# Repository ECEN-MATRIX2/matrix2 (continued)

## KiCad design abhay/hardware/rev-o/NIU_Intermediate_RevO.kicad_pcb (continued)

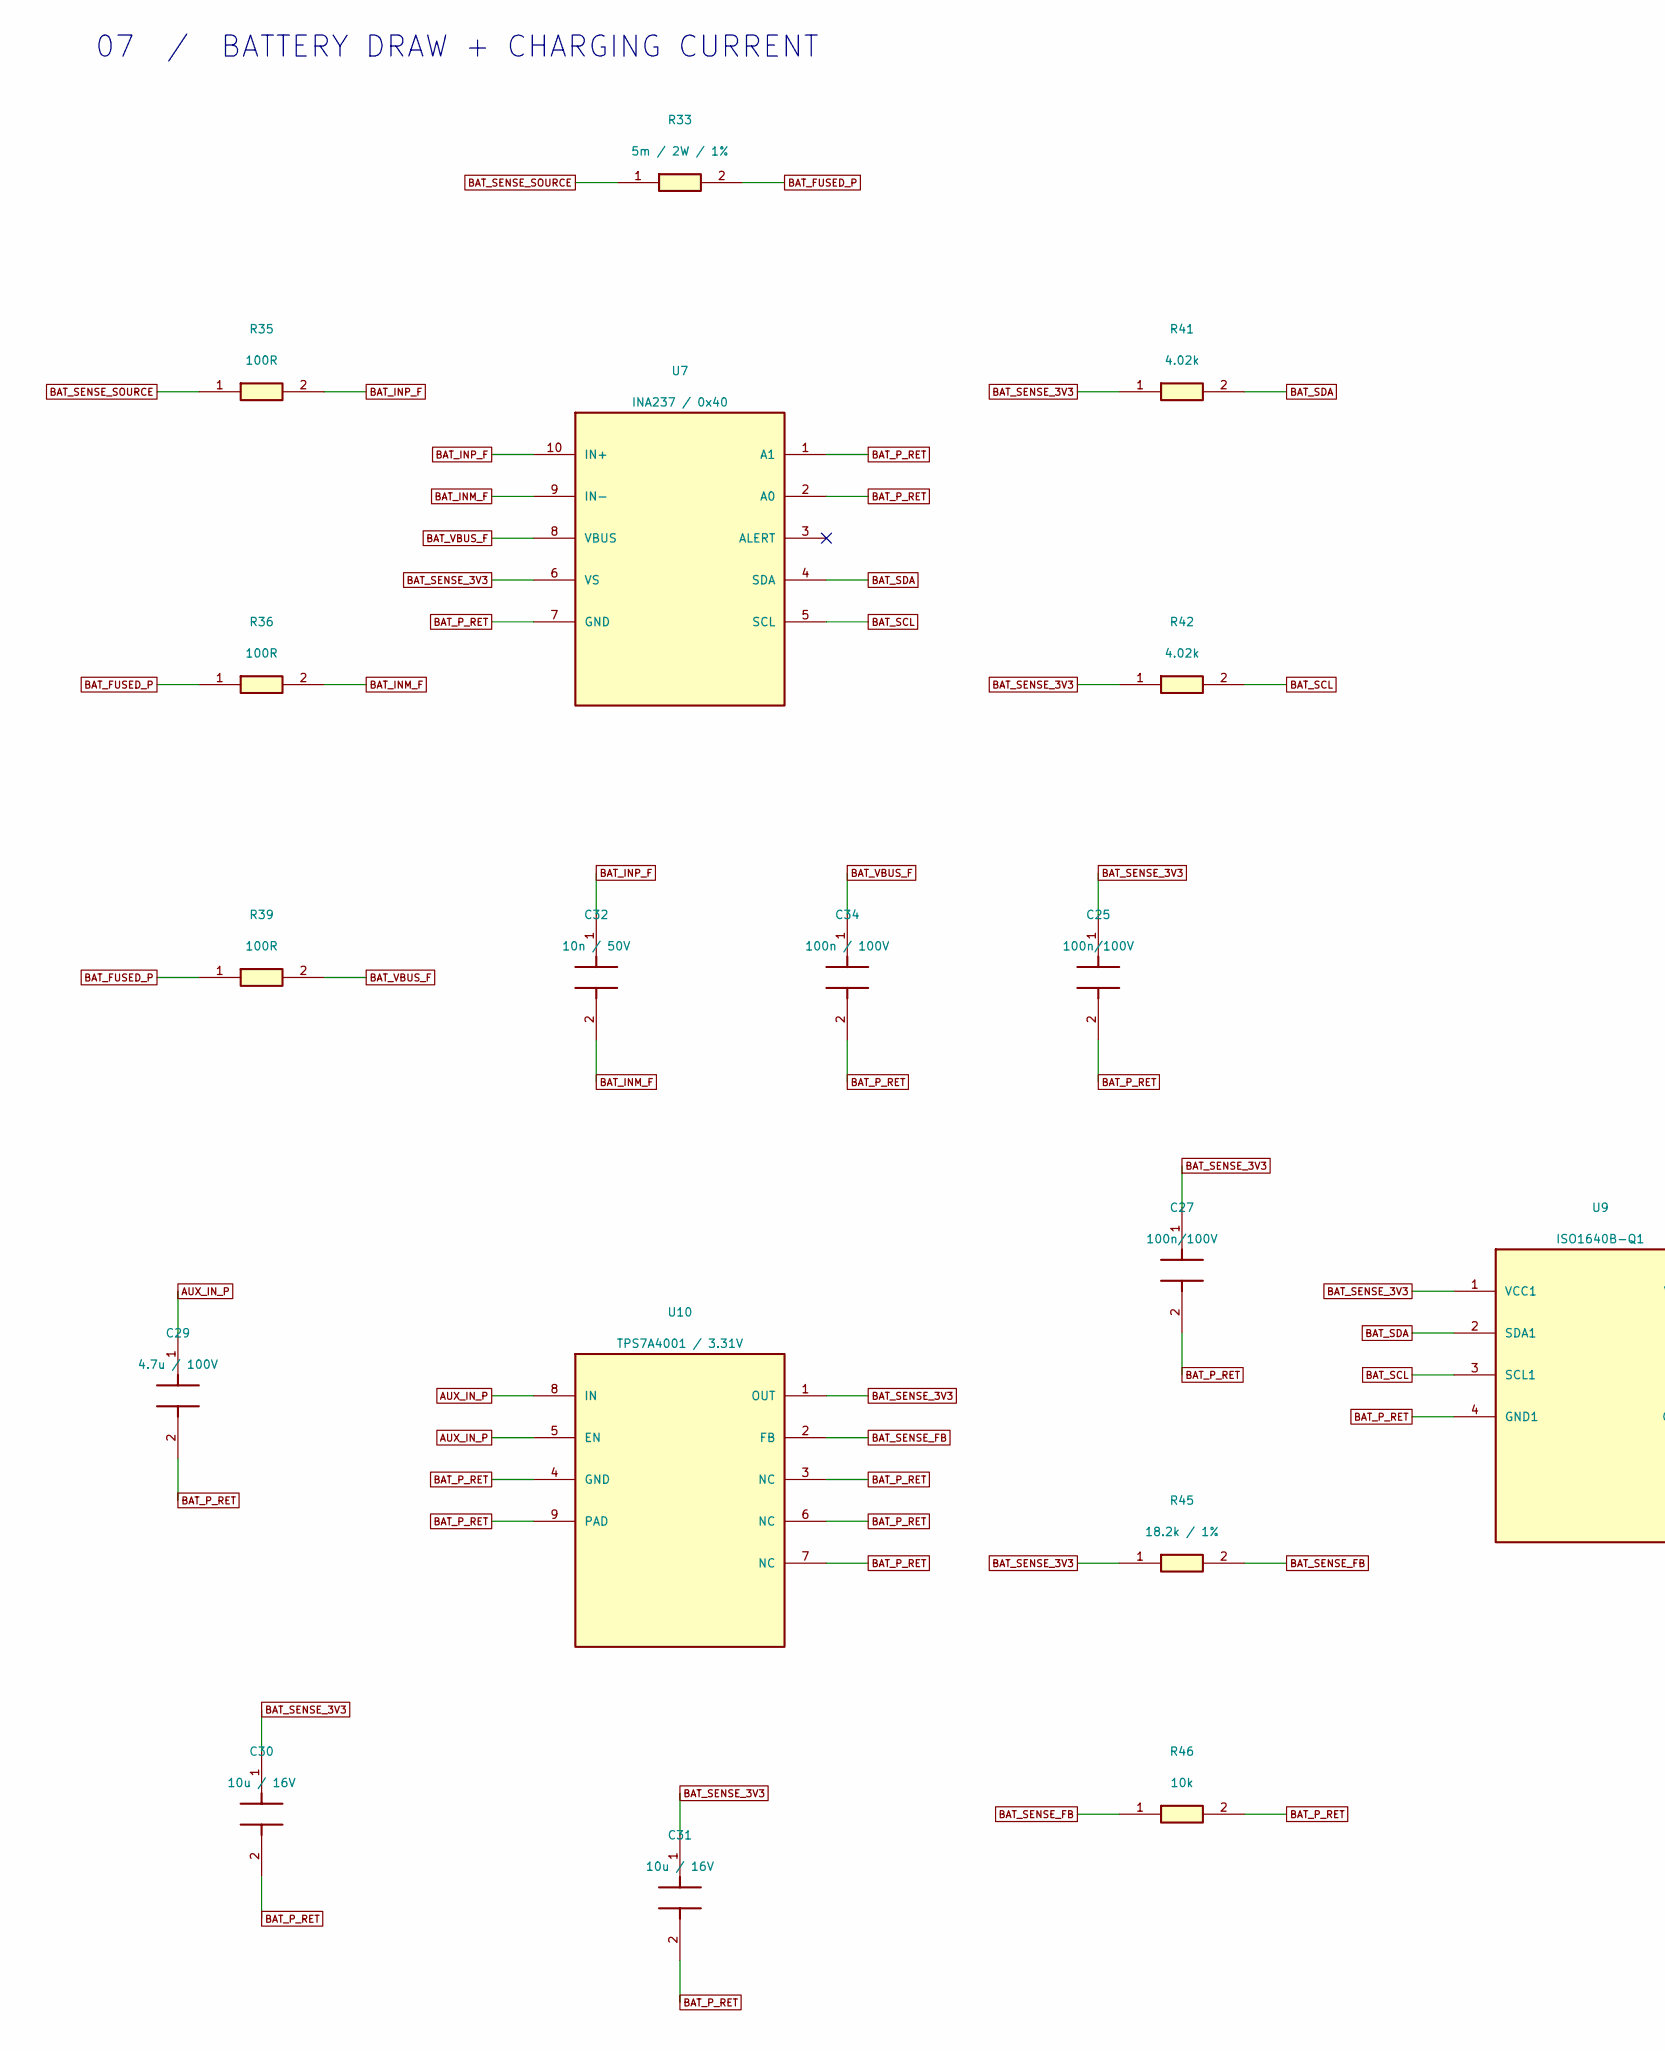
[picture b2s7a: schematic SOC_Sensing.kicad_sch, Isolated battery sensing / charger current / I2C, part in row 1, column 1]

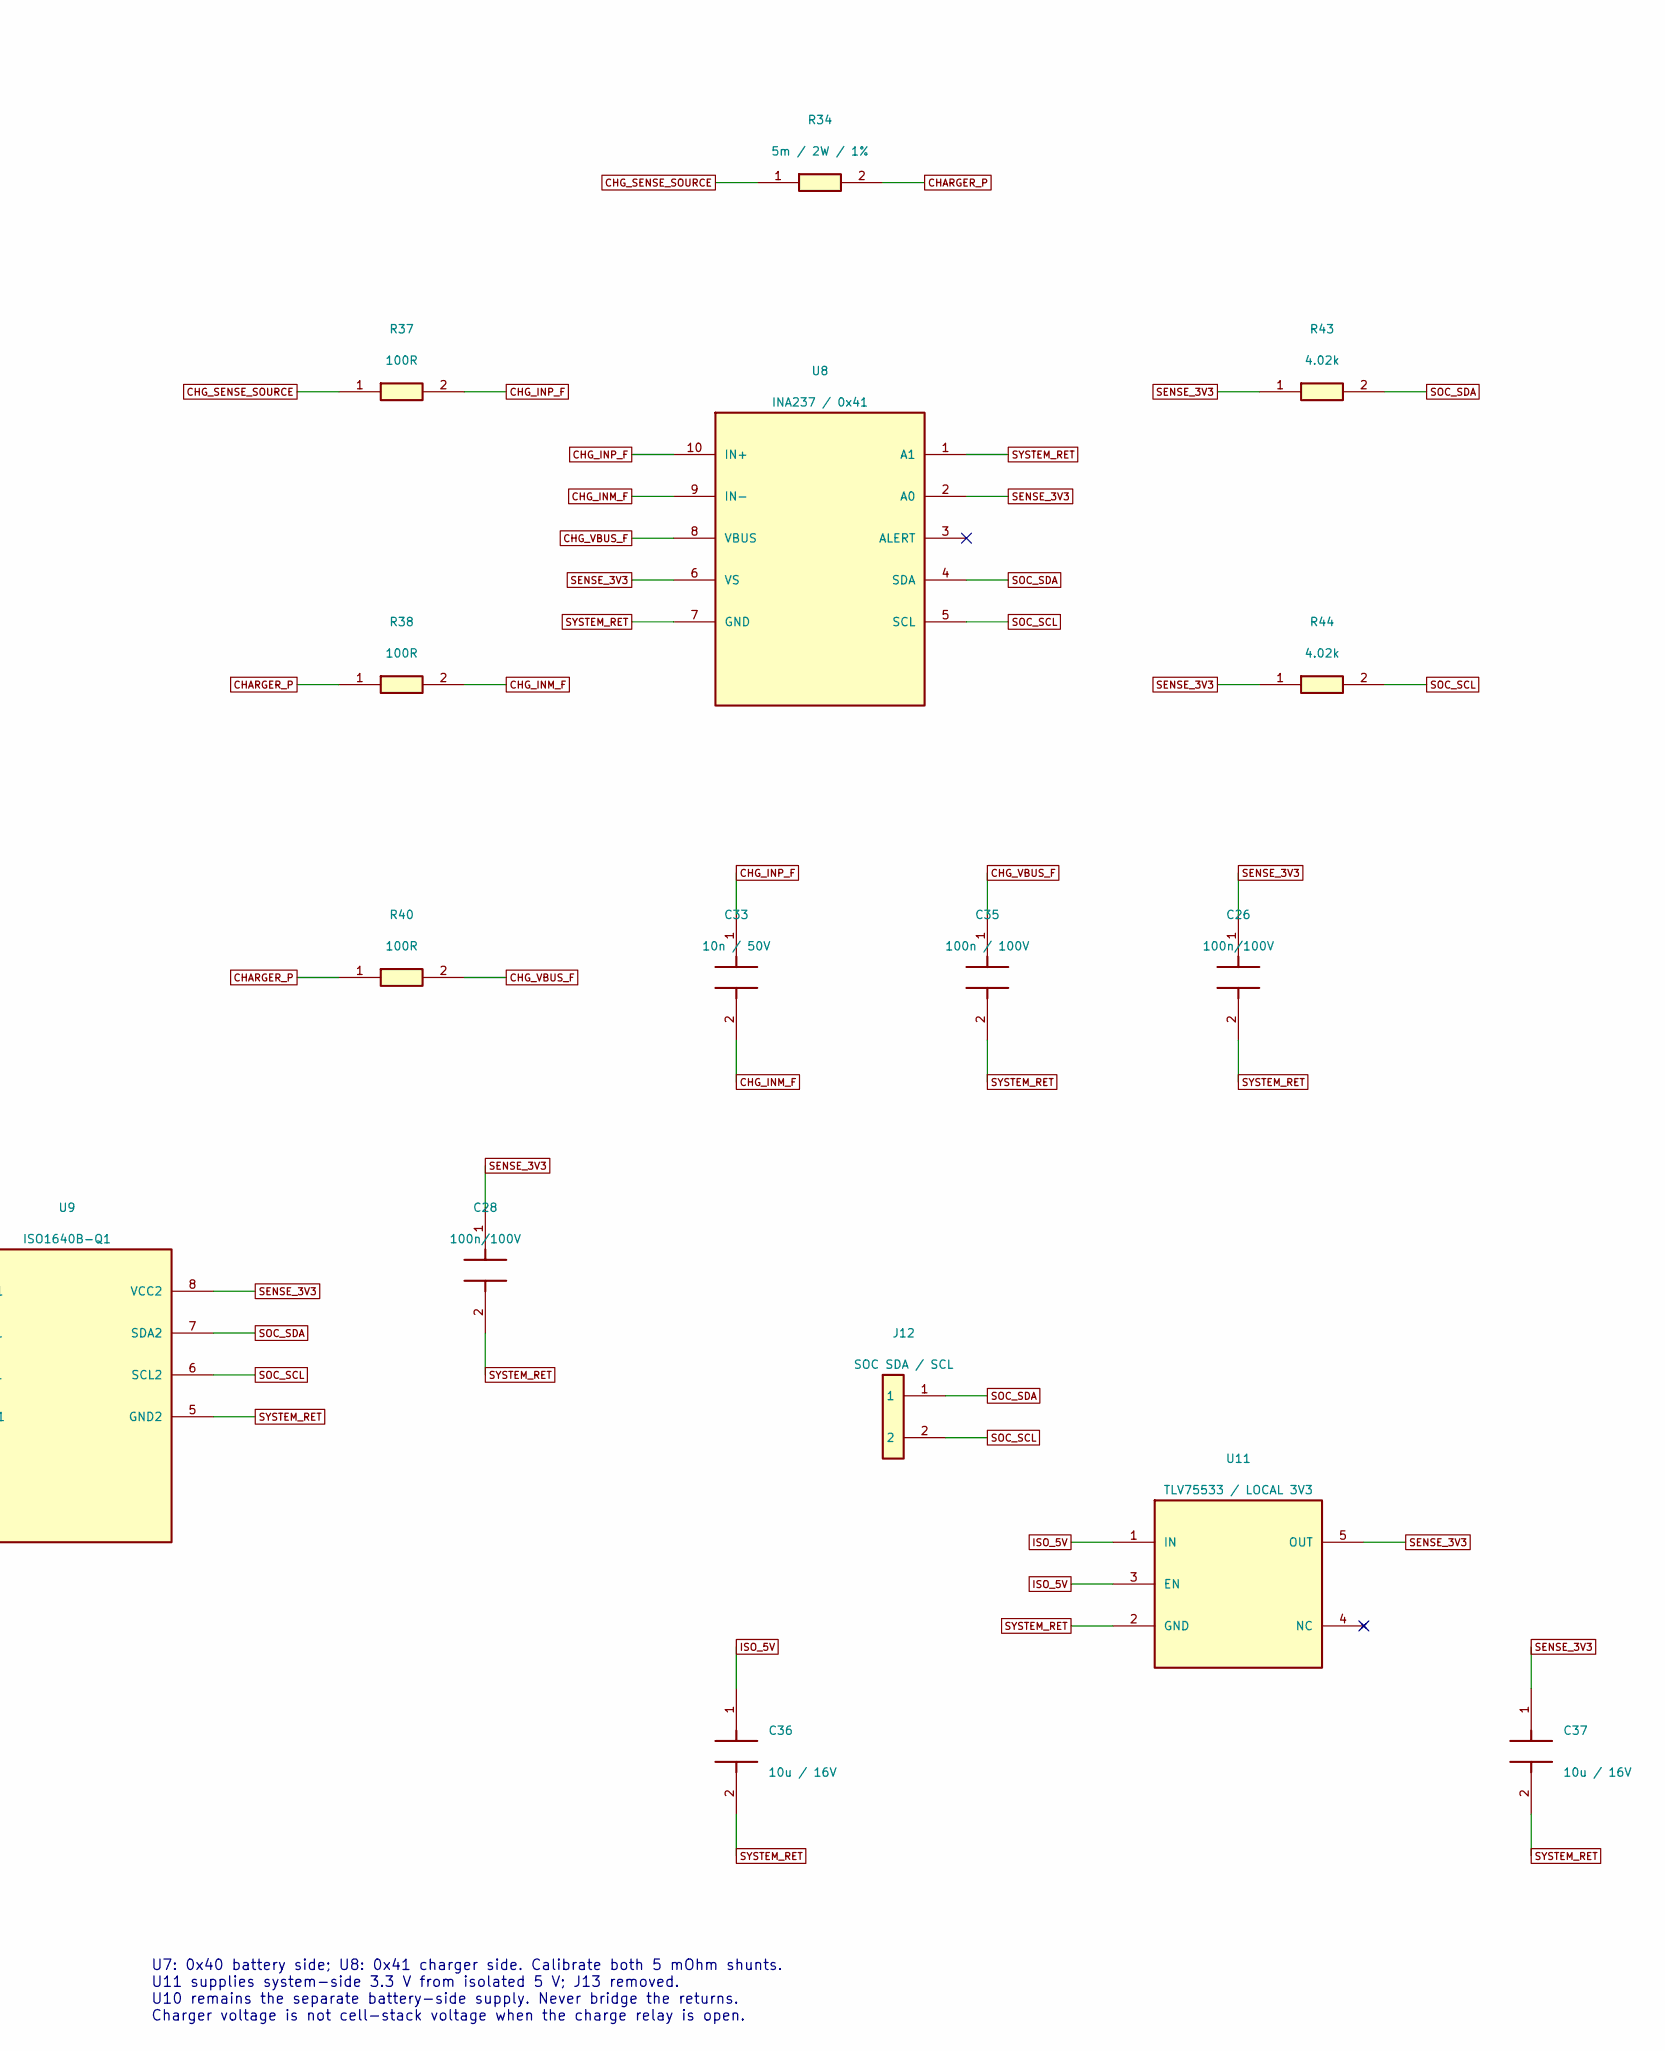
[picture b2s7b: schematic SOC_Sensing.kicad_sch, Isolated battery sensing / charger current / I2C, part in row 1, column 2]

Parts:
C25, C26, C27, C28: 100n/100V; C_0603_1608Metric; MPN GRM188R72A104KA35D; Mouser 81-GRM188R72A104KA35
C29: 4.7u / 100V; TDK_CNC6_1210_Recommended; MPN CNC6P1X7R2A475K250AE; Mouser 810-CNC6P1X7R2A475K2
C30, C31, C36, C37: 10u / 16V; C_0805_2012Metric; MPN C2012X5R1C106K085AC; Mouser 810-C2012X5R1C106K-2
C32, C33: 10n / 50V; C_0805_2012Metric; MPN C0805C103K5RACTU; Mouser 80-C0805C103K5R
C34, C35: 100n / 100V; C_0805_2012Metric; MPN C2012X7R2A104K125AA; Mouser 810-C2012X7R2A104K
J12: SOC SDA / SCL; PinHeader_1x02_P2.54mm_Vertical; MPN M20-9990245; Mouser 855-M20-9990245
R33, R34: 5m / 2W / 1%; Vishay_WSL2512_5m_6m9; MPN WSL25125L000FEA18; Mouser 71-WSL25125L000FEA18
R35, R36, R37, R38, R39, R40: 100R; R_0603_1608Metric; MPN RC0603FR-07100RL; Mouser 603-RC0603FR-07100RL
R41, R42, R43, R44: 4.02k; R_0603_1608Metric; MPN RT0603BRD074K02L; Mouser 603-RT0603BRD074K02L
R45: 18.2k / 1%; R_0603_1608Metric; MPN RT0603FRE0718K2L; Mouser 603-RT0603FRE0718K2L
R46: 10k; R_0603_1608Metric; MPN RT0603BRD0710KL; Mouser 603-RT0603BRD0710KL
U7: INA237 / 0x40; VSSOP-10_3x3mm_P0.5mm; MPN INA237AIDGSR; Mouser 595-INA237AIDGSR
U8: INA237 / 0x41; VSSOP-10_3x3mm_P0.5mm; MPN INA237AIDGSR; Mouser 595-INA237AIDGSR
U9: ISO1640B-Q1; SOIC-8_3.9x4.9mm_P1.27mm; MPN ISO1640BQDRQ1; Mouser 595-ISO1640BQDRQ1
U10: TPS7A4001 / 3.31V; TI_DGN0008B_3x3_0p65; MPN TPS7A4001DGNT; Mouser 595-TPS7A4001DGNT
U11: TLV75533 / LOCAL 3V3; SOT-23-5; MPN TLV75533PDBVR; Mouser 595-TLV75533PDBVR

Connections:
AUX_IN_P: C29.1, U10.5 (EN), U10.8 (IN); also elsewhere on the board
BAT_FUSED_P: R33.2, R36.1, R39.1; also elsewhere on the board
BAT_INM_F: C32.2, R36.2, U7.9 (IN-)
BAT_INP_F: C32.1, R35.2, U7.10 (IN+)
BAT_P_RET: C25.2, C27.2, C29.2, C30.2, C31.2, C34.2, R46.2, U7.1 (A1), U7.2 (A0), U7.7 (GND), U9.4 (GND1), U10.3 (NC), U10.4 (GND), U10.6 (NC), U10.7 (NC), U10.9 (PAD); also elsewhere on the board
BAT_SCL: R42.2, U7.5 (SCL), U9.3 (SCL1)
BAT_SDA: R41.2, U7.4 (SDA), U9.2 (SDA1)
BAT_SENSE_3V3: C25.1, C27.1, C30.1, C31.1, R41.1, R42.1, R45.1, U7.6 (VS), U9.1 (VCC1), U10.1 (OUT)
BAT_SENSE_FB: R45.2, R46.1, U10.2 (FB)
BAT_SENSE_SOURCE: R33.1, R35.1; also elsewhere on the board
BAT_VBUS_F: C34.1, R39.2, U7.8 (VBUS)
CHARGER_P: R34.2, R38.1, R40.1; also elsewhere on the board
CHG_INM_F: C33.2, R38.2, U8.9 (IN-)
CHG_INP_F: C33.1, R37.2, U8.10 (IN+)
CHG_SENSE_SOURCE: R34.1, R37.1; also elsewhere on the board
CHG_VBUS_F: C35.1, R40.2, U8.8 (VBUS)
ISO_5V: C36.1, U11.1 (IN), U11.3 (EN); also elsewhere on the board
SENSE_3V3: C26.1, C28.1, C37.1, R43.1, R44.1, U8.2 (A0), U8.6 (VS), U9.8 (VCC2), U11.5 (OUT)
SOC_SCL: J12.2, R44.2, U8.5 (SCL), U9.6 (SCL2)
SOC_SDA: J12.1, R43.2, U8.4 (SDA), U9.7 (SDA2)
SYSTEM_RET: C26.2, C28.2, C35.2, C36.2, C37.2, U8.1 (A1), U8.7 (GND), U9.5 (GND2), U11.2 (GND); also elsewhere on the board

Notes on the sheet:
07 / BATTERY DRAW + CHARGING CURRENT
U7: 0x40 battery side; U8: 0x41 charger side. Calibrate both 5 mOhm shunts. U11 supplies system-side 3.3 V from isolated 5 V; J13 removed. U10 remains the separate battery-side supply. Never bridge the returns. Charger voltage is not cell-stack voltage when the charge relay is open.

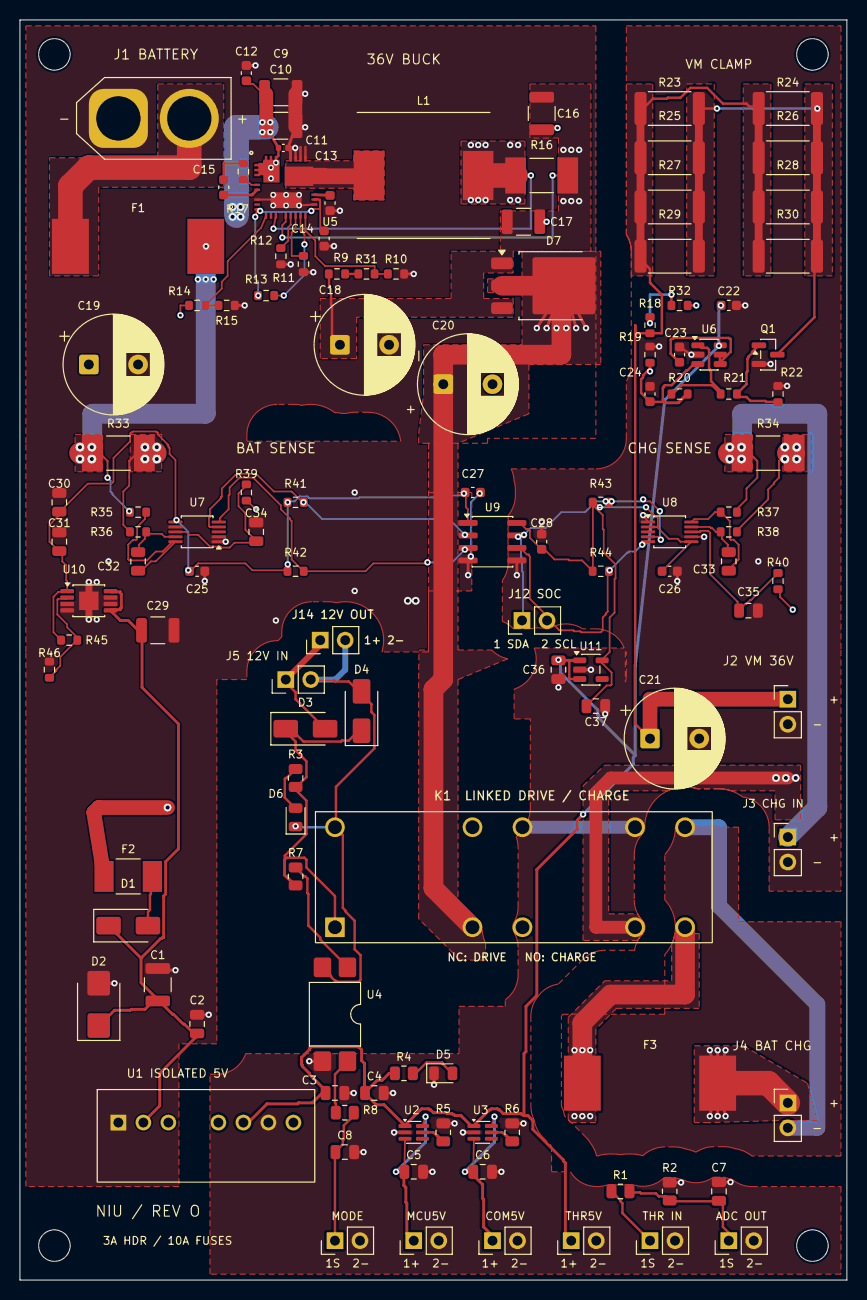
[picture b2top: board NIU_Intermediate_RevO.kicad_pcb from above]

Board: 4 copper layers, 84.0 x 128.0 mm, 124 parts (0 on the bottom side), 62 nets.

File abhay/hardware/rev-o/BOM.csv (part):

"Reference","Value","MPN","Mouser","Footprint","New in Rev O","Rating","Note"
"J1","BATTERY XT60","XT60-M","USER SUPPLIED","AMASS_XT60-M_Vertical_PositivePin1","No","54.6V max intended pack",""
"F1","10A / 125VDC","3403.0284.23","693-3403.0284.23","Fuse_SCHURTER_UMT-H_5.3x16","No","10A time lag; Schurter UMT-H",""
"K1","G7SA-2A2B DC12","G7SA-2A2B DC12","653-G7SA-2A2BDC12","Omron_G7SA_2A2B_TopView","No","2NC+2NO forcibly guided; 12V/30mA coil; 6A carry; DC load switching must be derated","One physical relay. 11-12 and 21-22 are NC drive contacts; 33-34 and 43-44 are NO charge contacts. Coil 0 positive, 1 negative. Near-zero-current transfer only; no loaded 36-54.6V switching approval. Header/harness current limit is lower than relay rating."
"J2","TO MOTOR VM","M20-9990245","855-M20-9990245","PinHeader_1x02_P2.54mm_Vertical","No","3A max per header contact; mating lead rating may be lower","0.64mm square pins at 2.54mm pitch. Ordinary female jumper sockets fit. External current limiting required for the actual harness; 10A fuse is not jumper overload protection."
"J3","FROM CHARGE IC","M20-9990245","855-M20-9990245","PinHeader_1x02_P2.54mm_Vertical","No","3A max per header contact; mating lead rating may be lower","0.64mm square pins at 2.54mm pitch. Ordinary female jumper sockets fit. External current limiting required for the actual harness; 10A fuse is not jumper overload protection."
"F3","10A / 125VDC","3403.0284.23","693-3403.0284.23","Fuse_SCHURTER_UMT-H_5.3x16","No","10A time lag; Schurter UMT-H",""
"J4","TO BATTERY CHARGE","M20-9990245","855-M20-9990245","PinHeader_1x02_P2.54mm_Vertical","No","3A max per header contact; mating lead rating may be lower","0.64mm square pins at 2.54mm pitch. Ordinary female jumper sockets fit. External current limiting required for the actual harness; 10A fuse is not jumper overload protection."
"J5","EXTERNAL 12V ONLY","M20-9990245","855-M20-9990245","PinHeader_1x02_P2.54mm_Vertical","No","3A header / LV signals",""
"D3","SS14","SS14-E3/61T","625-SS14-E3","D_SMA","No","40V 1A Schottky","Reverse input protection"
"D4","SS14 / FLYBACK","SS14-E3/61T","625-SS14-E3","D_SMA","No","40V 1A Schottky","Flyback diode across the single K1 coil; no shared-coil timing dependency."
"R3","4.7k","RC0805FR-074K7L","603-RC0805FR-074K7L","R_0805_2012Metric","No","1%, 0.125W",""
"D6","CHARGE / AMBER","LTST-C170KSKT","859-LTST-C170KSKT","LED_0805_2012Metric","No","0805 amber",""
"F2","1A / 125VDC","0454001.MR","576-0454001.MR","Fuse_Littelfuse_NANO2_452-454","No","1A time lag 125VDC",""
"D1","SS110","SS110-LTP","833-SS110-LTP","D_SMA","No","100V 1A Schottky","Auxiliary reverse polarity protection only"
"D2","SMBJ58A","SMBJ58A","652-SMBJ58A","D_SMB","No","58V standoff / 93.6V rated pulse clamp","Transient clamp only; not sustained overvoltage regulation 58 V standoff, unidirectional 600 W SMB TVS; same polarity/package. Replaces Littelfuse purchasing selection."
"C1","4.7u / 100V","CNC6P1X7R2A475K250AE","810-CNC6P1X7R2A475K2","TDK_CNC6_1210_Recommended","No","X7R, 10%, 1210; 3.2 x 2.5 x 2.5 mm","TDK CNC6 reflow lands applied: 1.1 x 2.5 mm pads, 2.2 mm gap. Nominal body height 2.5 mm. Correct underside orientation required. DC-bias effective capacitance and ripple remain bench checks."
"C2","100n / 100V","C2012X7R2A104K125AA","810-C2012X7R2A104K","C_0805_2012Metric","No","X7R, 10%, 0805",""
"U1","TMR 6-4811WI","TMR 6-4811WI","495-TMR6-4811WI","TRACO_TMR6WI_SIP8_TopView","No","18-75Vin; 5V/1.2A; functional isolation","Remote pin open = always on. Total demo 5V budget 500mA pending load/thermal verification."
"C3","10u / 16V","C2012X5R1C106K085AC","810-C2012X5R1C106K-2","C_0805_2012Metric","No","X5R, 10%, 0805, 0.85 mm height","Stocked but NRND (not recommended for new designs) per Mouser. Selected for this MVP; not obsolete or special order."
"C4","100n/100V","C2012X7R2A104K125AA","810-C2012X7R2A104K","C_0805_2012Metric","No","X7R, 10%, 0805","Voltage rating increased from 50 V to 100 V; same capacitance and package. Shares C2 purchasing SKU."
"R4","2.2k","RC0805FR-072K2L","603-RC0805FR-072K2L","R_0805_2012Metric","No","1% 0.125W",""
"D5","5V ON / GREEN","LTST-C170KGKT","859-LTST-C170KGKT","LED_0805_2012Metric","No","0805 green",""
"U2","LM66100DCKR","LM66100DCKR","595-LM66100DCKR","SOT-363_SC-70-6","No","1.5-5.5V / 1.5A","CE tied to output for reverse-current blocking. Unused ST grounded through explicit 0-ohm configuration link."
"R5","0R / ST GND LINK","RC0805JR-070RL","603-RC0805JR-070RL","R_0805_2012Metric","No","0 ohm configuration link","Grounds unused ST as recommended by TI; removable for diagnostics."
"C5","1u / 16V","GRM21BR71C105KA01L","81-GRM40X105K16L","C_0805_2012Metric","No","X7R 0805, 16V",""
"J6","MCU 5V OUT","M20-9990245","855-M20-9990245","PinHeader_1x02_P2.54mm_Vertical","No","3A header / LV signals",""
"U3","LM66100DCKR","LM66100DCKR","595-LM66100DCKR","SOT-363_SC-70-6","No","1.5-5.5V / 1.5A","CE tied to output for reverse-current blocking. Unused ST grounded through explicit 0-ohm configuration link."
"R6","0R / ST GND LINK","RC0805JR-070RL","603-RC0805JR-070RL","R_0805_2012Metric","No","0 ohm configuration link","Grounds unused ST as recommended by TI; removable for diagnostics."
"C6","1u / 16V","GRM21BR71C105KA01L","81-GRM40X105K16L","C_0805_2012Metric","No","X7R 0805, 16V",""
"J7","COMM 5V OUT","M20-9990245","855-M20-9990245","PinHeader_1x02_P2.54mm_Vertical","No","3A header / LV signals",""
"J8","THROTTLE POWER","M20-9990245","855-M20-9990245","PinHeader_1x02_P2.54mm_Vertical","No","3A header / LV signals",""
"J9","THROTTLE SIGNAL","M20-9990245","855-M20-9990245","PinHeader_1x02_P2.54mm_Vertical","No","3A header / LV signals",""
"R1","12.1k / 1%","RC0805FR-0712K1L","603-RC0805FR-0712K1L","R_0805_2012Metric","No","1% 0.125W",""
"R2","15k / 1%","RC0805FR-0715KL","603-RC0805FR-0715KL","R_0805_2012Metric","No","1% 0.125W",""
"C7","100n/100V","C2012X7R2A104K125AA","810-C2012X7R2A104K","C_0805_2012Metric","No","X7R, 10%, 0805","Voltage rating increased from 50 V to 100 V; same capacitance and package. Shares C2 purchasing SKU."
"J10","MCU THROTTLE ADC","M20-9990245","855-M20-9990245","PinHeader_1x02_P2.54mm_Vertical","No","3A header / LV signals",""
"U4","LTV-817S-B","LTV-817S-B","859-LTV-817S-B","SMDIP-4_W9.53mm","No","Optocoupler; CTR 130-260% at 5mA","Isolated charge-mode indication only; no hardware motor inhibit."
"R7","2k / 1%","RC0805FR-072KL","603-RC0805FR-072KL","R_0805_2012Metric","No","1% 0.125W","Approximately 5mA optocoupler LED current from protected external 12V."
"R8","1k / 1%","RC0805FR-071KL","603-RC0805FR-071KL","R_0805_2012Metric","No","1% 0.125W","Series protection for open-collector GPIO connection."
"C8","10n / 50V","C0805C103K5RACTU","80-C0805C103K5R","C_0805_2012Metric","No","X7R, 10%, 0805","Noise filter; uses MCU internal 3.3V pull-up."
"J11","CHARGE MODE / RETURN","M20-9990245","855-M20-9990245","PinHeader_1x02_P2.54mm_Vertical","No","3A header / LV signals",""
"U5","LM70860RRXR","LM70860RRXR","595-LM70860RRXR","TI_RRX0029B_6x6","No","80V input; 6A target; AUTO; internal compensation","BIAS to return because output exceeds 30V. Controller ground pad 30 required."
"R9","442k","RT0603BRD07442KL","603-RT0603BRD07442KL","R_0603_1608Metric","No","0.1%, 25 ppm/K, 0603","Use 442k + new 4.02k R31 = 446.02k. Replaces unavailable 446k; preserves buck setpoint within 0.0016 V nominal."
"R10","10k","RT0603BRD0710KL","603-RT0603BRD0710KL","R_0603_1608Metric","No","0.1% except R17 1%",""
"R11","49.9k","RT0603BRD0749K9L","603-RT0603BRD0749K9L","R_0603_1608Metric","No","0.1% except R17 1%",""
"R12","29.4k","RT0603BRD0729K4L","603-RT0603BRD0729K4L","R_0603_1608Metric","No","0.1% except R17 1%",""
"R13","100k","TNPW0603100KBEEA","71-TNPW0603100KBEEA","R_0603_1608Metric","No","0.1%, 25 ppm/K, 0603",""
"R14","383k","RT0603BRD07383KL","603-RT0603BRD07383KL","R_0603_1608Metric","No","0.1% except R17 1%",""
"R15","10k","RT0603BRD0710KL","603-RT0603BRD0710KL","R_0603_1608Metric","No","0.1% except R17 1%",""
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
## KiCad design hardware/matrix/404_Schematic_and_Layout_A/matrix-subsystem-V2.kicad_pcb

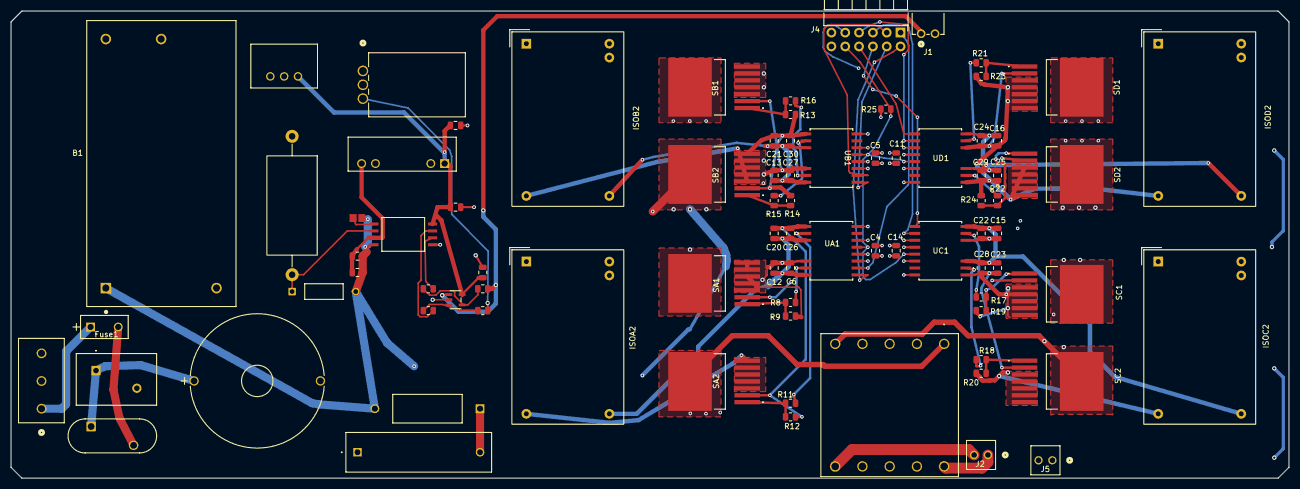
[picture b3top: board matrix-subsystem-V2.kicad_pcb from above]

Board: 4 copper layers, 234.6 x 85.8 mm, 83 parts (0 on the bottom side), 56 nets.

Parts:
B1: RAC20-12SK_277; CONV_RAC20-12SK_277
B2: R-785.0-0.5; R-785.0-0.5_RCP
B3: R-78K2.5-2.0L; R-78K-2p0L_RCP
C1: 0.22uF X2 305VAC SAFETY CAP; CAP_B32933A3224K000_TDK
C2: C0805C224J1RACTU; CAPC220145_140N_KEM
C3, C4, C5, C8, C10, C11, C12, C13, C14, C15, C16, C20, C21, C23, C25: C0805C104K5RACTU; C_0805_2012Metric
C6, C7, C9, C22, C24, C26, C27, C28, C29, C30: C0805C105K3RACTU; C_0805_2012Metric
Fuse1: 39211000000; FUS_LITTELFUSE_392_LTF
ISOA2: MDS03F-15
ISOB2: MDS03F-15
ISOC2: MDS03F-15
ISOD2: MDS03F-15
J1: TSW-102-08-L-S-RA; TSW-102-08-L-S-RA_Edge
J2, J5: 640452-2; 640452-2_TYC
J3: 1729131; CONN_1729131_PXC
J4: PH2RA-12-UA
L1: 1422512C; 1422512C_MUR
MOV1: TMOV14RP275EL2T7; TMOV14RP275E
NTCThermistor1: SL15 5R007; TRES_SL15 5R007_AMT
R1: 4.7R FLAMEPROOF/FUSIBLE, MAINS-RATED; YAG_RSF100_YAG
R2, R4: 8.20k 0.1%; R_0805_2012Metric
R3, R10: 20.0k 0.1%; R_0805_2012Metric
R5: VR68000006204JAC00 — 6.2M 1W HV; R_Axial_DIN0918_L18.0mm_D9.0mm_P25.40mm_Horizontal
R7: 68.1k 1%; YAG_MF25_YAG
R8, R11, R15, R16, R17, R18, R21, R22: RC0805FR-0710RL; R_0805_2012Metric
R9, R12, R13, R14, R19, R20, R23, R24: RC0805FR-0710KL; R_0805_2012Metric
R25: 10k EN FAIL-SAFE PULLDOWN; R_0805_2012Metric
SA1, SA2: C3M0045065J1; C3M0025065J1
SB1, SB2: C3M0045065J1; C3M0025065J1
SC1, SC2: C3M0045065J1; C3M0025065J1
SD1, SD2: C3M0045065J1; C3M0025065J1
T1: TDK EFD25/13/9 N87: P=32T pins 1-5; S=7T pins 10-6; B66422W1010D001_TDK
U1: ISO224ADWVR; DWV8_TEX
U2: TLV9061IDBVR; DBV5_TEX
U3: REM1-0505S; REM1_RCP
UA1: UCC21530DWKR; SOIC14_7P6X10P5_TEX
UB1: UCC21530DWKR; SOIC14_7P6X10P5_TEX
UC1: UCC21530DWKR; SOIC14_7P6X10P5_TEX
UD1: UCC21530DWKR; SOIC14_7P6X10P5_TEX

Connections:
12V_SAFE: B1.5 (+VOUT), B2.1 (+VIN), B3.1 (+VIN), ISOA2.1 (+Vin), ISOB2.1 (+Vin), ISOC2.1 (+Vin), ISOD2.1 (+Vin), J4.11, J5.1
/A (+): SA2.8 (D), SB1.8 (D), T1.1 (Vp+)
/ADC_OUT: J1.1, R2.2, U2.1 (OUT)
/B (-): SC2.8 (D), SD1.8 (D), T1.5 (Vp-)
/HFAC_26V25_100k_N: J2.2, T1.6 (Vs-)
/HFAC_26V25_100k_P: J2.1, T1.10 (Vs+)
/MAINS_L: Fuse1.1, J3.1
/Matrix Converter/+15V_A: C6.1, C12.1, C20.1, C26.1, ISOA2.13 (+Vout), UA1.11 (VDDB), UA1.16 (VDDA)
/Matrix Converter/+15V_B: C13.1, C21.1, C27.1, C30.1, ISOB2.13 (+Vout), UB1.11 (VDDB), UB1.16 (VDDA)
/Matrix Converter/+15V_C: C15.1, C22.1, C23.1, C28.1, ISOC2.13 (+Vout), UC1.11 (VDDB), UC1.16 (VDDA)
/Matrix Converter/+15V_D: C16.1, C24.1, C25.1, C29.1, ISOD2.13 (+Vout), UD1.11 (VDDB), UD1.16 (VDDA)
/Matrix Converter/DRV_SA1: R8.2, UA1.15 (OUTA)
/Matrix Converter/DRV_SA2: R11.2, UA1.10 (OUTB)
/Matrix Converter/DRV_SB1: R16.2, UB1.15 (OUTA)
/Matrix Converter/DRV_SB2: R15.2, UB1.10 (OUTB)
/Matrix Converter/DRV_SC1: R17.2, UC1.15 (OUTA)
/Matrix Converter/DRV_SC2: R18.2, UC1.10 (OUTB)
/Matrix Converter/DRV_SD1: R21.2, UD1.15 (OUTA)
/Matrix Converter/DRV_SD2: R22.2, UD1.10 (OUTB)
/Matrix Converter/G_SA1: R8.1, R9.1, SA1.1 (G)
/Matrix Converter/G_SA2: R11.1, R12.1, SA2.1 (G)
/Matrix Converter/G_SB1: R13.1, R16.1, SB1.1 (G)
/Matrix Converter/G_SB2: R14.1, R15.1, SB2.1 (G)
/Matrix Converter/G_SC1: R17.1, R19.1, SC1.1 (G)
/Matrix Converter/G_SC2: R18.1, R20.1, SC2.1 (G)
/Matrix Converter/G_SD1: R21.1, R23.1, SD1.1 (G)
/Matrix Converter/G_SD2: R22.1, R24.1, SD2.1 (G)
/Matrix Converter/S_SA: C6.2, C12.2, C20.2, C26.2, ISOA2.12 (-Vout), R9.2, R12.2, SA1.2 (DS), SA1.3 (PS1), SA1.4 (PS2), SA1.5 (PS3), SA1.6 (PS4), SA1.7 (PS5), SA2.2 (DS), SA2.3 (PS1), SA2.4 (PS2), SA2.5 (PS3), SA2.6 (PS4), SA2.7 (PS5), UA1.9 (VSSB), UA1.14 (VSSA)
/Matrix Converter/S_SB: C13.2, C21.2, C27.2, C30.2, ISOB2.12 (-Vout), R13.2, R14.2, SB1.2 (DS), SB1.3 (PS1), SB1.4 (PS2), SB1.5 (PS3), SB1.6 (PS4), SB1.7 (PS5), SB2.2 (DS), SB2.3 (PS1), SB2.4 (PS2), SB2.5 (PS3), SB2.6 (PS4), SB2.7 (PS5), UB1.9 (VSSB), UB1.14 (VSSA)
/Matrix Converter/S_SC: C15.2, C22.2, C23.2, C28.2, ISOC2.12 (-Vout), R19.2, R20.2, SC1.2 (DS), SC1.3 (PS1), SC1.4 (PS2), SC1.5 (PS3), SC1.6 (PS4), SC1.7 (PS5), SC2.2 (DS), SC2.3 (PS1), SC2.4 (PS2), SC2.5 (PS3), SC2.6 (PS4), SC2.7 (PS5), UC1.9 (VSSB), UC1.14 (VSSA)
/Matrix Converter/S_SD: C16.2, C24.2, C25.2, C29.2, ISOD2.12 (-Vout), R23.2, R24.2, SD1.2 (DS), SD1.3 (PS1), SD1.4 (PS2), SD1.5 (PS3), SD1.6 (PS4), SD1.7 (PS5), SD2.2 (DS), SD2.3 (PS1), SD2.4 (PS2), SD2.5 (PS3), SD2.6 (PS4), SD2.7 (PS5), UD1.9 (VSSB), UD1.14 (VSSA)
/PWM SA1: J4.2, UA1.1 (INA)
/PWM SA2: J4.1, UA1.2 (INB)
/PWM SB1: J4.4, UB1.1 (INA)
/PWM SB2: J4.3, UB1.2 (INB)
/PWM SC1: J4.6, UC1.1 (INA)
/PWM SC2: J4.5, UC1.2 (INB)
/PWM SD1: J4.8, UD1.1 (INA)
/PWM SD2: J4.7, UD1.2 (INB)
/Variable Input/+2.5V: B3.3 (+VOUT), R4.2
/Variable Input/+5V: B2.3 (+VOUT), C8.1, C9.1, C10.1, U1.8 (VDD2), U2.5 (V+), U3.1 (+VIN)
/Variable Input/ISO_+5V: C3.1, C7.1, U1.3 (VDD1), U3.7 (+VOUT)
/Variable Input/U2_NEG: R2.1, R3.1, U2.4 (IN-)
/Variable Input/U2_POS: R4.1, R10.1, U2.3 (IN+)
AC_L_IN: B1.2 (VAC_IN(L)), C1.1, L1.2, R5.1, SA1.8 (D), SC1.8 (D)
AC_N_IN: B1.1 (VAC_IN(N)), C2.2, C3.2, C7.2, J3.2, MOV1.2, R1.2, R7.2, SB2.8 (D), SD2.8 (D), U1.4 (GND1), U3.6 (-VOUT)
COLD_GND: B1.4 (-VOUT), B2.2 (GND), B3.2 (GND), C4.2, C5.2, C8.2, C9.2, C10.2, C11.2, C14.2, ISOA2.23 (-Vin), ISOA2.24 (-Vin), ISOB2.23 (-Vin), ISOB2.24 (-Vin), ISOC2.23 (-Vin), ISOC2.24 (-Vin), ISOD2.23 (-Vin), ISOD2.24 (-Vin), J1.2, J4.12, J5.2, R25.1, U1.5 (GND2), U2.2 (V-), U3.2 (-VIN), UA1.4 (GND), UB1.4 (GND), UC1.4 (GND), UD1.4 (GND)
FPGA_3V3: C4.1, C5.1, C11.1, C14.1, J4.9, UA1.3 (VCCI), UA1.6 (DT), UA1.8 (VCCI), UB1.3 (VCCI), UB1.6 (DT), UB1.8 (VCCI), UC1.3 (VCCI), UC1.6 (DT), UC1.8 (VCCI), UD1.3 (VCCI), UD1.6 (DT), UD1.8 (VCCI)
GATE_EN: J4.10, R25.2, UA1.5 (EN), UB1.5 (EN), UC1.5 (EN), UD1.5 (EN)
unnamed: C1.2, R1.1
unnamed: Fuse1.2, NTCThermistor1.2
unnamed: L1.1, MOV1.1, NTCThermistor1.1
unnamed: R5.2, R7.1, U1.2 (IN)
unnamed: R3.2, U1.6 (OUTN)
unnamed: R10.2, U1.7 (OUTP)
unnamed: C2.1, U1.1 (VCAP)
